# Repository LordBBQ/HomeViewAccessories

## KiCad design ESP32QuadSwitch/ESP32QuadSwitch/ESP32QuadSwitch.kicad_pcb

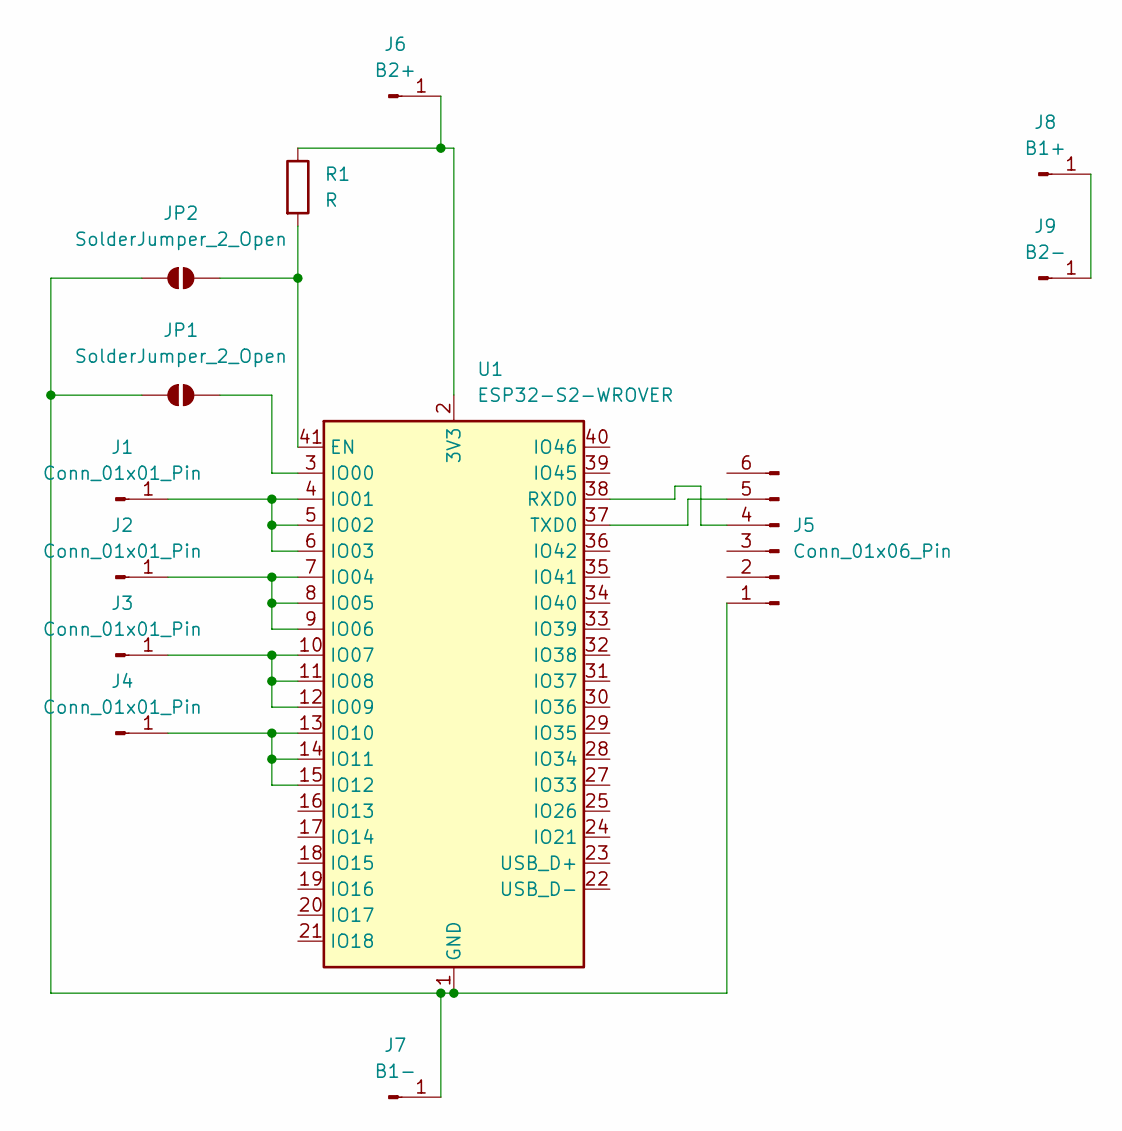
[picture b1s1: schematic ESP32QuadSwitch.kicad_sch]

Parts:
J1, J2, J3, J4: Conn_01x01_Pin; MountingHole_3.2mm_M3_DIN965_Pad
J5: Conn_01x06_Pin; PinHeader_1x06_P2.54mm_Vertical
J6: B2+; SolderWire-0.75sqmm_1x01_D1.25mm_OD3.5mm
J7: B1-; SolderWire-0.75sqmm_1x01_D1.25mm_OD3.5mm
J8: B1+; SolderWire-0.75sqmm_1x01_D1.25mm_OD3.5mm
J9: B2-; SolderWire-0.75sqmm_1x01_D1.25mm_OD3.5mm
JP1, JP2: SolderJumper_2_Open; SolderJumper-2_P1.3mm_Open_TrianglePad1.0x1.5mm
R1: R; R_0603_1608Metric_Pad0.98x0.95mm_HandSolder
U1: ESP32-S2-WROVER

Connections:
unnamed: J1.1, U1.4 (IO01), U1.5 (IO02), U1.6 (IO03)
unnamed: J2.1, U1.7 (IO04), U1.8 (IO05), U1.9 (IO06)
unnamed: J3.1, U1.10 (IO07), U1.11 (IO08), U1.12 (IO09)
unnamed: J4.1, U1.13 (IO10), U1.14 (IO11), U1.15 (IO12)
unnamed: J5.1, J7.1, JP1.1 (A), JP2.1 (A), U1.1 (GND), U1.26 (GND), U1.42 (GND), U1.43 (GND)
unnamed: J5.4, U1.38 (RXD0)
unnamed: J5.5, U1.37 (TXD0)
unnamed: J6.1, R1.1, U1.2 (3V3)
unnamed: J8.1, J9.1
unnamed: JP1.2 (B), U1.3 (IO00)
unnamed: JP2.2 (B), R1.2, U1.41 (EN)

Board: 2 copper layers, 13 parts (0 on the bottom side), 11 nets, no tracks yet.

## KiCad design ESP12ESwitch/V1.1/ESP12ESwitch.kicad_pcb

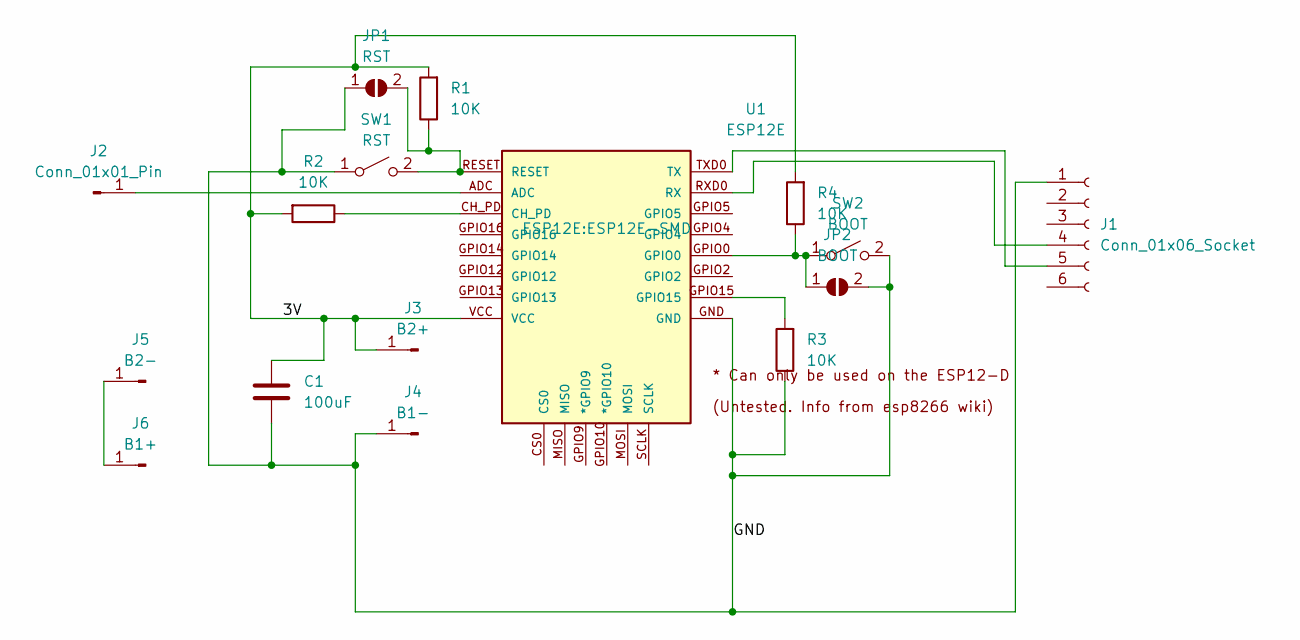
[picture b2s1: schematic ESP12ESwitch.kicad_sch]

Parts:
C1: 100uF; C_0402_1005Metric_Pad0.74x0.62mm_HandSolder
J1: Conn_01x06_Socket; PinHeader_1x06_P2.54mm_Vertical
J2: Conn_01x01_Pin; MountingHole_3.2mm_M3_DIN965_Pad
J3: B2+; PinHeader_1x01_P2.54mm_Vertical
J4: B1-; PinHeader_1x01_P2.54mm_Vertical
J5: B2-; PinHeader_1x01_P2.54mm_Vertical
J6: B1+; PinHeader_1x01_P2.54mm_Vertical
JP1: RST; SolderJumper-2_P1.3mm_Open_Pad1.0x1.5mm
JP2: BOOT; SolderJumper-2_P1.3mm_Open_Pad1.0x1.5mm
R1, R2, R3, R4: 10K; R_0603_1608Metric_Pad0.98x0.95mm_HandSolder
SW1: RST; 5mmButton
SW2: BOOT; 5mmButton
U1: ESP12E; ESP12E-SMD

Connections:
/3V: C1.1, J3.1, R1.2, R2.2, R4.2, U1.VCC
/GND: C1.2, J1.1, J4.1, JP1.1 (A), JP2.2 (B), R3.1, SW1.1 (A), SW2.2 (B), U1.GND
unnamed: J1.4, U1.RXD0 (RX)
unnamed: J1.5, U1.TXD0 (TX)
unnamed: J2.1, U1.ADC
unnamed: J5.1, J6.1
unnamed: JP1.2 (B), R1.1, SW1.2 (B), U1.RESET
unnamed: JP2.1 (A), R4.1, SW2.1 (A), U1.GPIO0
unnamed: R2.1, U1.CH_PD
unnamed: R3.2, U1.GPIO15

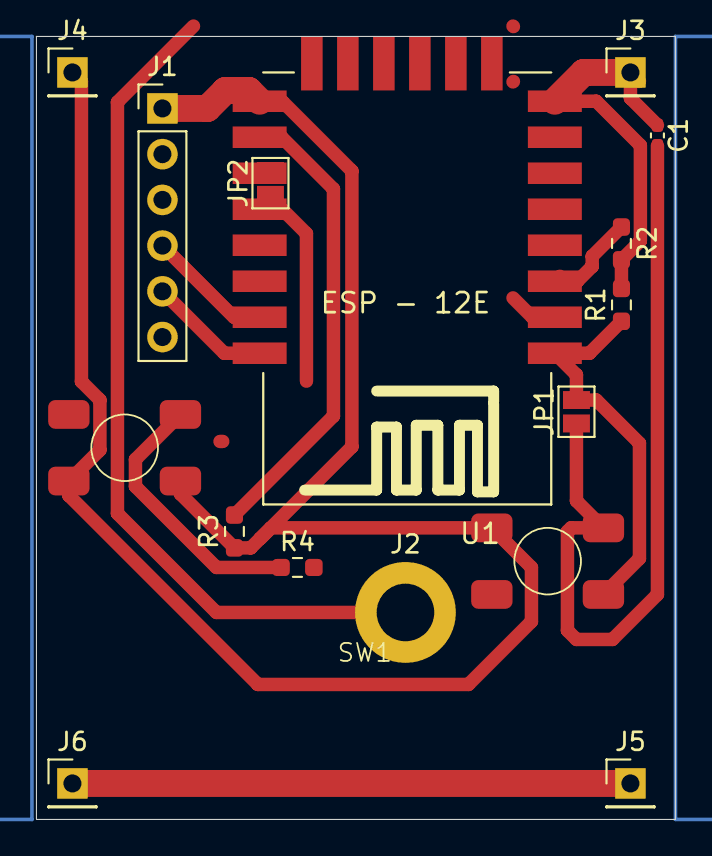
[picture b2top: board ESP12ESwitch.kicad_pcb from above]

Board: 2 copper layers, 35.5 x 43.5 mm, 16 parts (0 on the bottom side), 10 nets.

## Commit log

2024-03-07 began pcb and schematic
2024-03-11 made footprint for aliexpress button
2024-03-12 started automation
2024-03-14 improved layout
2024-03-15 finalised layout, added cu fill
2024-04-03 migrated into v1, v1.1 folders. New layout
2024-04-09 began ESP32s2 based switch
2024-04-10 new PCB with esp32-s2
